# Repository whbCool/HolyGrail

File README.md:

# TEA@CPP Escape Room 2026: The Holy Grail

The _Holy Grail_ is a custom PCB, designed for the Indiana Jones puzzle as a part of TEA@CPP's "Retro Rewind" 2026 Escape Room. 

This repository includes the KiCad schematic, as well as the code database for the board.

For more details on the code, check out [the introductory walkthrough here](walkthrough.md).

Major Components:
- ESP32-WROOM-32UE
- SC16IS752IPW_128
- CD74HC138QM96Q1
- SN74LVC1G125DBVT
- CDCLVC1106PWR
- 7447715003
- LMR33640
- AP63205WU-7
- 5747842-2
- W5500
- USBLC6-2SC6
- TMJ0026ABNL
- MMBT3904
- CP2102N-A02-GQFN24
- 1812L150_24MR
- LM393DR

Design Requirements:
1. Read data from 12 LD2410C sensors using SPI-to-UART converters.
2. Aggregate sensor data and package it into a JSON payload to be sent to an MQTT broker.
3. USB port for programming and debugging.

More Info: https://drive.google.com/drive/folders/14Y64IZpTN127Q0mva5SdtTZ1QgllTaBJ

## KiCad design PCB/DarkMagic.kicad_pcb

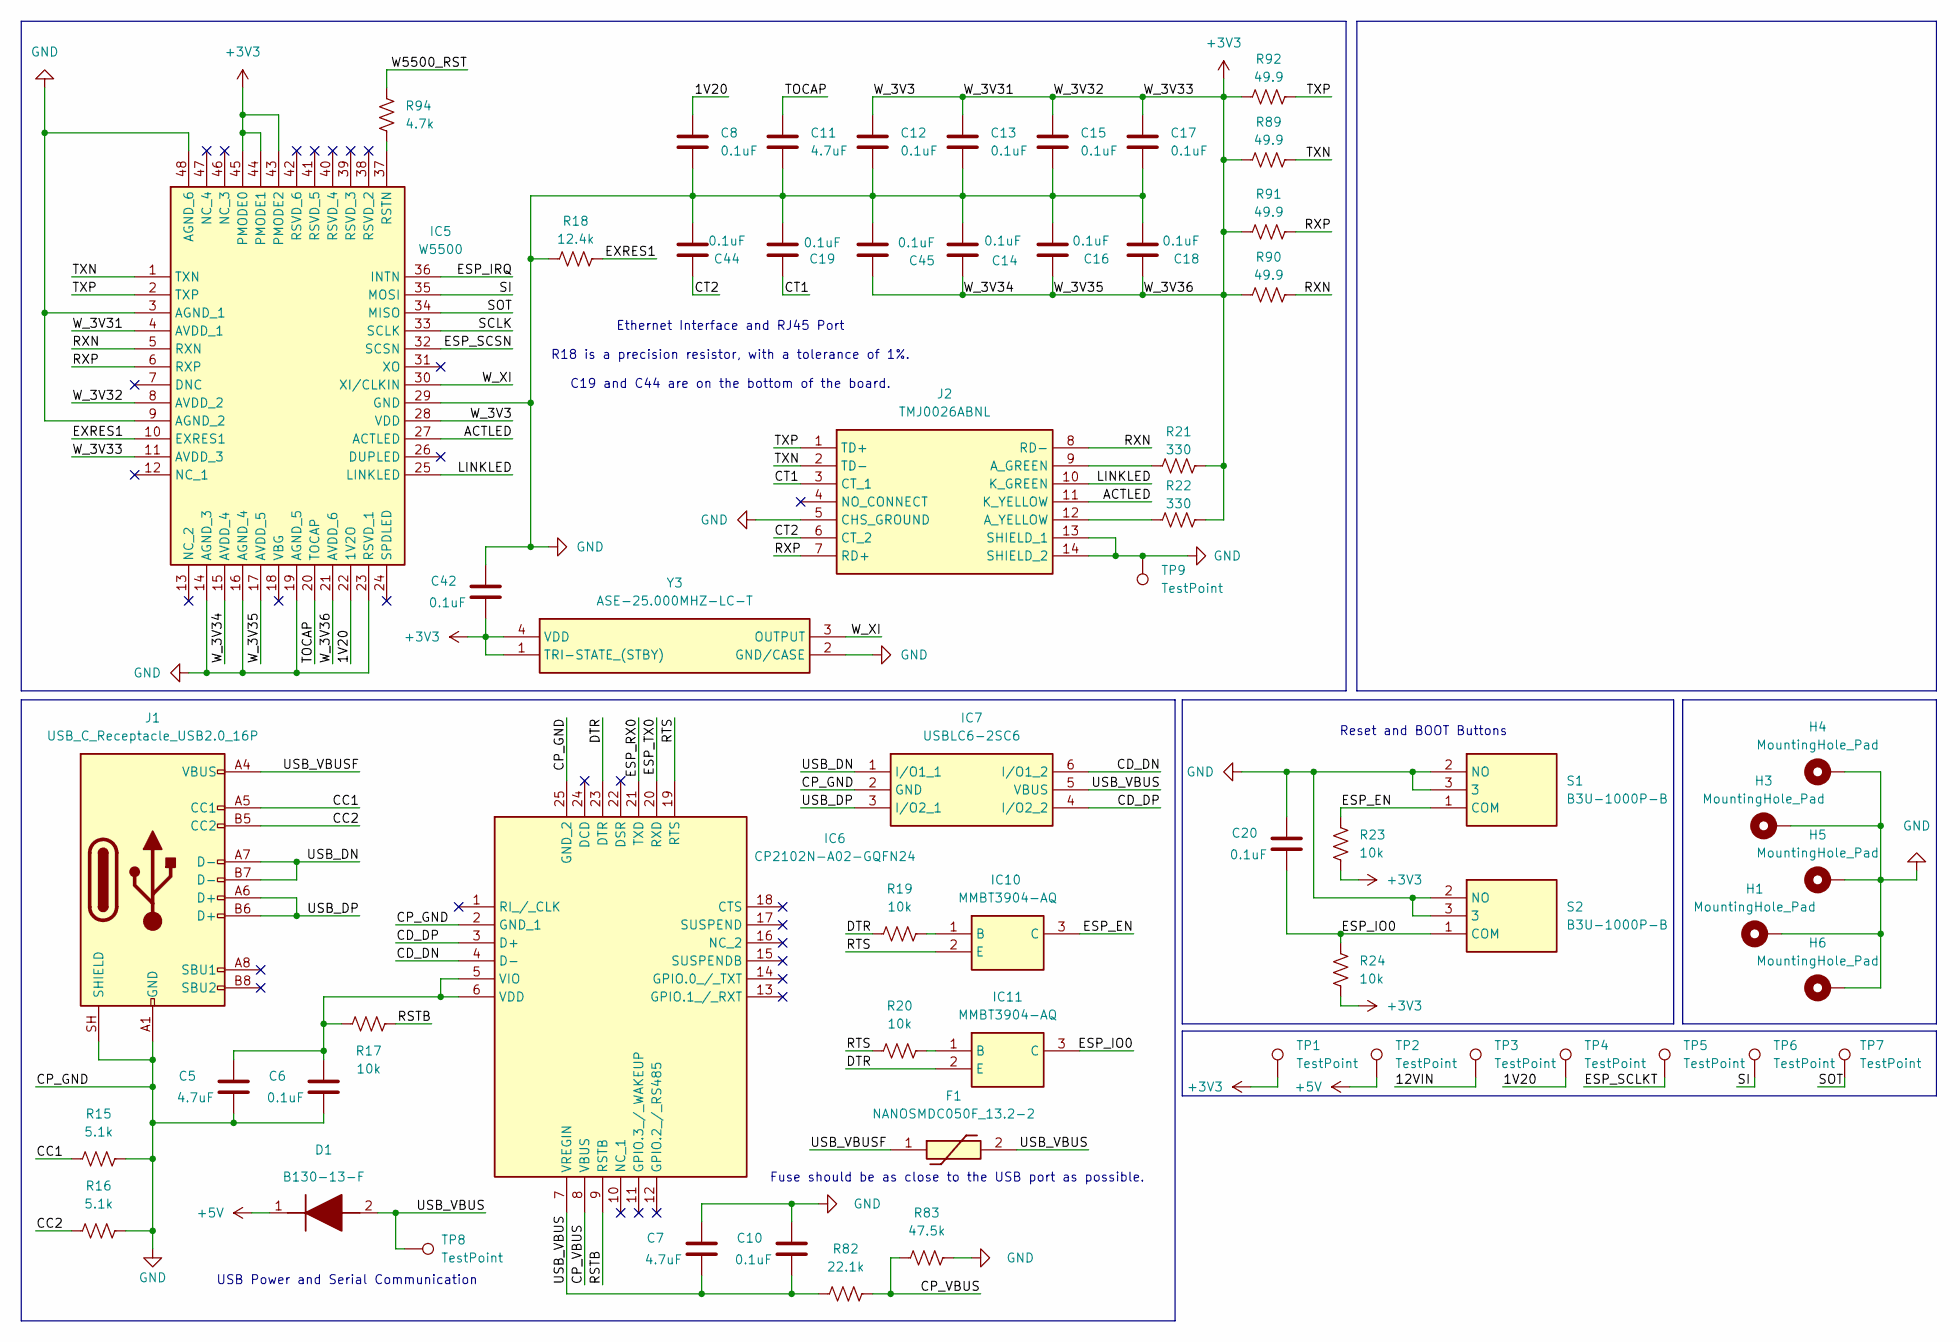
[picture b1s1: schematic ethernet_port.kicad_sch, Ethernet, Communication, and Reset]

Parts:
C5, C7: 4.7uF; C_0805_2012Metric_Pad1.18x1.45mm_HandSolder; Manufacturer_Part_Number CL21A475KACLRNC; Mouser Part Number 187-CL21A475KACLRNC
C6, C8, C10, C12, C13, C14, C15, C16, C17, C18, C19, C20, C42, C44, C45: 0.1uF; C_0805_2012Metric_Pad1.18x1.45mm_HandSolder; Manufacturer_Part_Number CL21B104KCC5PNC; Mouser Part Number 187-CL21B104KCC5PNC
C11: 4.7uF; C_0805_2012Metric_Pad1.18x1.45mm_HandSolder; Manufacturer_Part_Number CL21B103KC6WPNC; Mouser Part Number 187-CL21B103KC6WPNC
D1: B130-13-F; DIOM5226X230N; Mouser Part Number 621-B130-F
F1: NANOSMDC050F_13.2-2; FUSC3216X74N; Mouser Part Number 650-NANOC050F/13.2-2
H1, H3, H4, H5, H6: MountingHole_Pad; MountingHole_3.2mm_M3_MOD
IC5: W5500; QFP50P900X900X160-48N; Mouser Part Number 950-W5500
IC6: CP2102N-A02-GQFN24; QFN50P400X400X80-25N-D; Mouser Part Number 634-CP2102NA02GQFN24
IC7: USBLC6-2SC6; SOT95P280X145-6N; Mouser Part Number 511-USBLC6-2SC6
IC10, IC11: MMBT3904-AQ; SOT95P240X120-3N; Mouser Part Number 637-MMBT3904-AQ
J1: USB_C_Receptacle_USB2.0_16P; USB_C_Receptacle_GCT_USB4105-xx-A_16P_TopMnt_Horizontal; Manufacturer_Part_Number UJ20-C-H-G-SMT-1A-P16-TR; Mouser Part Number 179-CHGSMT1AP16TR
J2: TMJ0026ABNL; Mouser Part Number 960-TMJ0026ABNL
R15, R16: 5.1k; R_0805_2012Metric_Pad1.20x1.40mm_HandSolder; Manufacturer_Part_Number ERA-6ARB512V; Mouser Part Number 667-ERA-6ARB512V
R17, R19, R20, R23, R24: 10k; R_0805_2012Metric_Pad1.20x1.40mm_HandSolder; Manufacturer_Part_Number ERA-6AEB103V; Mouser Part Number 667-ERA-6AEB103V
R18: 12.4k; R_0805_2012Metric_Pad1.20x1.40mm_HandSolder; Manufacturer_Part_Number ERJ-UP6F1242V; Mouser Part Number 667-ERJ-UP6F1242V
R21, R22: 330; R_0805_2012Metric_Pad1.20x1.40mm_HandSolder; Manufacturer_Part_Number ERJ-PC6B3300V; Mouser Part Number 667-ERJ-PC6B3300V
R82: 22.1k; R_0805_2012Metric_Pad1.20x1.40mm_HandSolder; Manufacturer_Part_Number ERA-6AEB2212V; Mouser Part Number 667-ERA-6AEB2212V
R83: 47.5k; R_0805_2012Metric_Pad1.20x1.40mm_HandSolder; Manufacturer_Part_Number ERA-6AEB4752V; Mouser Part Number 667-ERA-6AEB4752V
R89, R90, R91, R92: 49.9; R_0805_2012Metric_Pad1.20x1.40mm_HandSolder; Manufacturer_Part_Number ERJ-P06F49R9V; Mouser Part Number 667-ERJ-P06F49R9V
R94: 4.7k; R_0805_2012Metric_Pad1.20x1.40mm_HandSolder; Manufacturer_Part_Number ERA-6AEB103V; Mouser Part Number 667-ERA-6AEB103V
S1, S2: B3U-1000P-B; B3U1000PB; Mouser Part Number 653-B3U-1000P-B
TP1, TP2, TP3, TP4, TP5, TP6, TP7, TP8, TP9: TestPoint; TestPoint_Pad_D3.0mm
Y3: ASE-25.000MHZ-LC-T; ASE25000MHZLCT; Mouser Part Number 815-ASE-25.000MHZ-LC-T

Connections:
+5V: D1.1 (K), TP2.1 (1_1); also elsewhere on the board
/1V20: C8.1, IC5.22 (1V2O), TP4.1 (1_1)
/12VIN: TP3.1 (1_1); also elsewhere on the board
/ACTLED: IC5.27 (ACTLED), J2.11 (K_YELLOW)
/CC1: J1.A5 (CC1), R15.1
/CC2: J1.B5 (CC2), R16.1
/CD_DN: IC6.4 (D-), IC7.6 (I/O1_2)
/CD_DP: IC6.3 (D+), IC7.4 (I/O2_2)
/CP_VBUS: IC6.8 (VBUS), R82.1, R83.1
/CT1: C19.2, J2.3 (CT_1)
/CT2: C44.1, J2.6 (CT_2)
/DTR: IC6.23 (DTR), IC11.2 (E), R19.1
/ESP_EN: IC10.3 (C), R23.2, S1.1 (COM); also elsewhere on the board
/ESP_IO0: C20.1, IC11.3 (C), R24.2, S2.1 (COM); also elsewhere on the board
/ESP_IRQ: IC5.36 (INTN); also elsewhere on the board
/ESP_RX0: IC6.21 (TXD); also elsewhere on the board
/ESP_SCLKT: TP5.1 (1_1); also elsewhere on the board
/ESP_SCSN: IC5.32 (SCSN); also elsewhere on the board
/ESP_TX0: IC6.20 (RXD); also elsewhere on the board
/EXRES1: IC5.10 (EXRES1), R18.2
/LINKLED: IC5.25 (LINKLED), J2.10 (K_GREEN)
/RSTB: IC6.9 (RSTB), R17.2
/RTS: IC6.19 (RTS), IC10.2 (E), R20.1
/RXN: IC5.5 (RXN), J2.8 (RD-), R90.2
/RXP: IC5.6 (RXP), J2.7 (RD+), R91.2
/SCLK: IC5.33 (SCLK); also elsewhere on the board
/SI: IC5.35 (MOSI), TP6.1 (1_1); also elsewhere on the board
/SOT: IC5.34 (MISO), TP7.1 (1_1); also elsewhere on the board
/TOCAP: C11.1, IC5.20 (TOCAP)
/TXN: IC5.1 (TXN), J2.2 (TD-), R89.2
/TXP: IC5.2 (TXP), J2.1 (TD+), R92.2
/USB_DN: IC7.1 (I/O1_1), J1.A7 (D-), J1.B7 (D-)
/USB_DP: IC7.3 (I/O2_1), J1.A6 (D+), J1.B6 (D+)
/USB_VBUS: C7.1, C10.1, D1.2 (A), F1.2, IC6.7 (VREGIN), IC7.5 (VBUS), R82.2, TP8.1 (1_1)
/USB_VBUSF: F1.1, J1.A4 (VBUS), J1.A9 (VBUS), J1.B4 (VBUS), J1.B9 (VBUS)
/W5500_RST: R94.1; also elsewhere on the board
/W_XI: IC5.30 (XI/CLKIN), Y3.3 (OUTPUT)
unnamed: IC5.37 (RSTN), R94.2
unnamed: C5.2, C6.2, IC6.5 (VIO), IC6.6 (VDD), R17.1
unnamed: IC10.1 (B), R19.2
unnamed: IC11.1 (B), R20.2
unnamed: J2.9 (A_GREEN), R21.1
unnamed: J2.12 (A_YELLOW), R22.1

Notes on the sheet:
Ethernet Interface and RJ45 Port R18 is a precision resistor, with a tolerance of 1%. C19 and C44 are on the bottom of the board.
USB Power and Serial Communication
Reset and BOOT Buttons
Fuse should be as close to the USB port as possible.

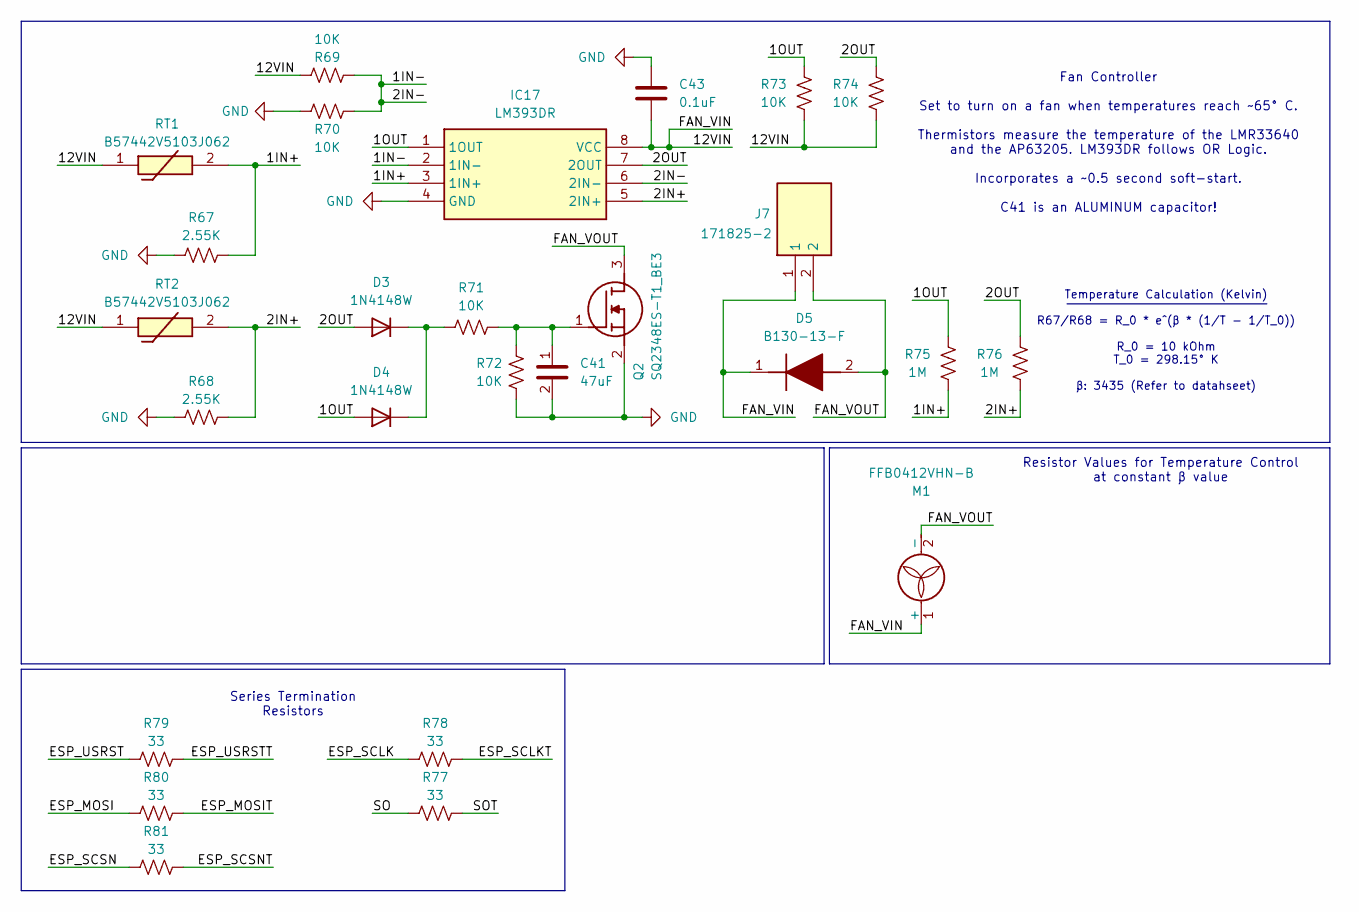
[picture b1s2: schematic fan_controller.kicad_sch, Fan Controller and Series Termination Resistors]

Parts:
C41: 47uF; C_Elec_10x10.2; Manufacturer_Part_Number EEH-ZA1K470P; Mouser Part Number 667-EEH-ZA1K470P
C43: 0.1uF; C_0805_2012Metric_Pad1.18x1.45mm_HandSolder; Manufacturer_Part_Number CL21B104KCC5PNC; Mouser Part Number 187-CL21B104KCC5PNC
D3, D4: 1N4148W; D_SOD-123; Manufacturer_Part_Number 1N4148W-7-F; Mouser Part Number 621-1N4148W-7-F
D5: B130-13-F; DIOM5226X230N; Mouser Part Number 621-B130-F
IC17: LM393DR; SOIC127P600X175-8N; Mouser Part Number 595-LM393DR
J7: 171825-2; SHDR2W69P0X250_1X2_500X530X1040P; Mouser Part Number 571-171825-2
M1: FFB0412VHN-B; Manufacturer_Part_Number FFB0412VHN-B; Mouser Part Number 108-FFB0412VHN-B
Q2: SQ2348ES-T1_BE3; SOT95P237X112-3N; Mouser Part Number 78-SQ2348ES-T1_BE3
R67, R68: 2.55K; R_0805_2012Metric_Pad1.20x1.40mm_HandSolder; Manufacturer_Part_Number ERA-6AEB2551V; Mouser Part Number 667-ERA-6AEB2551V
R69, R70, R71, R72, R73, R74: 10K; R_0805_2012Metric_Pad1.20x1.40mm_HandSolder; Manufacturer_Part_Number ERA-6APB103V; Mouser Part Number 667-ERA-6APB103V
R75, R76: 1M; R_0805_2012Metric_Pad1.20x1.40mm_HandSolder; Manufacturer_Part_Number ERA-6AEB105V; Mouser Part Number 667-ERA-6AEB105V
R77, R78, R79, R80, R81: 33; R_0805_2012Metric_Pad1.20x1.40mm_HandSolder; Manufacturer_Part_Number ERA-6AHD330V; Mouser Part Number 667-ERA-6AHD330V
RT1, RT2: B57442V5103J062; THRMC2012X130N; Mouser Part Number 871-B57442V5103J62

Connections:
/1IN+: IC17.3 (1IN+), R67.1, R75.1, RT1.2
/1IN-: IC17.2 (1IN-), IC17.6 (2IN-), R69.2, R70.1
/1OUT: D4.2 (A), IC17.1 (1OUT), R73.2, R75.2
/2IN+: IC17.5 (2IN+), R68.1, R76.1, RT2.2
/2OUT: D3.2 (A), IC17.7 (2OUT), R74.2, R76.2
/12VIN: C43.2, D5.1 (K), IC17.8 (VCC), J7.1, M1.1 (+), R69.1, R73.1, R74.1, RT1.1, RT2.1; also elsewhere on the board
/ESP_MOSI: R80.2; also elsewhere on the board
/ESP_MOSIT: R80.1; also elsewhere on the board
/ESP_SCLK: R78.2; also elsewhere on the board
/ESP_SCLKT: R78.1; also elsewhere on the board
/ESP_SCSN: R81.2; also elsewhere on the board
/ESP_SCSNT: R81.1; also elsewhere on the board
/ESP_USRST: R79.2; also elsewhere on the board
/ESP_USRSTT: R79.1; also elsewhere on the board
/FAN_VOUT: D5.2 (A), J7.2, M1.2 (-), Q2.3 (D)
/SO: R77.2; also elsewhere on the board
/SOT: R77.1; also elsewhere on the board
unnamed: D3.1 (K), D4.1 (K), R71.1
unnamed: C41.1, Q2.1 (G), R71.2, R72.2

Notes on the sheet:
Resistor Values for Temperature Control at constant β value
Series Termination Resistors
Fan Controller Set to turn on a fan when temperatures reach ~65° C. Thermistors measure the temperature of the LMR33640 and the AP63205. LM393DR follows OR Logic. Incorporates a ~0.5 second soft-start. C41 is an ALUMINUM capacitor!
Temperature Calculation (Kelvin) R67/R68 = R_0 * e^(β * (1/T - 1/T_0)) R_0 = 10 kOhm T_0 = 298.15° K β: 3435 (Refer to datahseet)

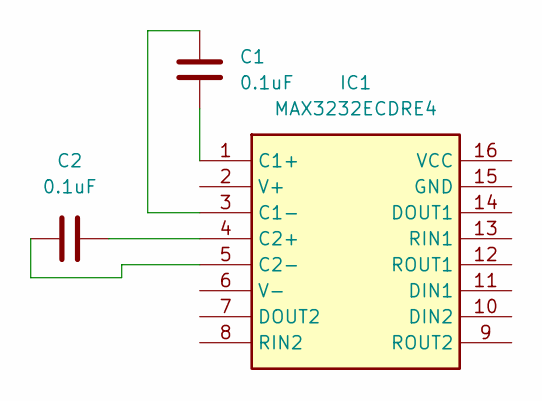
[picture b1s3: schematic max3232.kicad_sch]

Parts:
C1, C2: 0.1uF
IC1: MAX3232ECDRE4; SOIC127P600X175-16N; Manufacturer_Part_Number MAX3232ECDRE4; Mouser Part Number 595-MAX3232ECDRE4

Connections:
/XS1T: IC1.6 (Y4); also elsewhere on the board
/XS3T: IC1.14 (Y1); also elsewhere on the board
/XS4T: IC1.9 (Y5); also elsewhere on the board
/XS5T: IC1.11 (Y2); also elsewhere on the board
/XS6T: IC1.13 (Y3); also elsewhere on the board

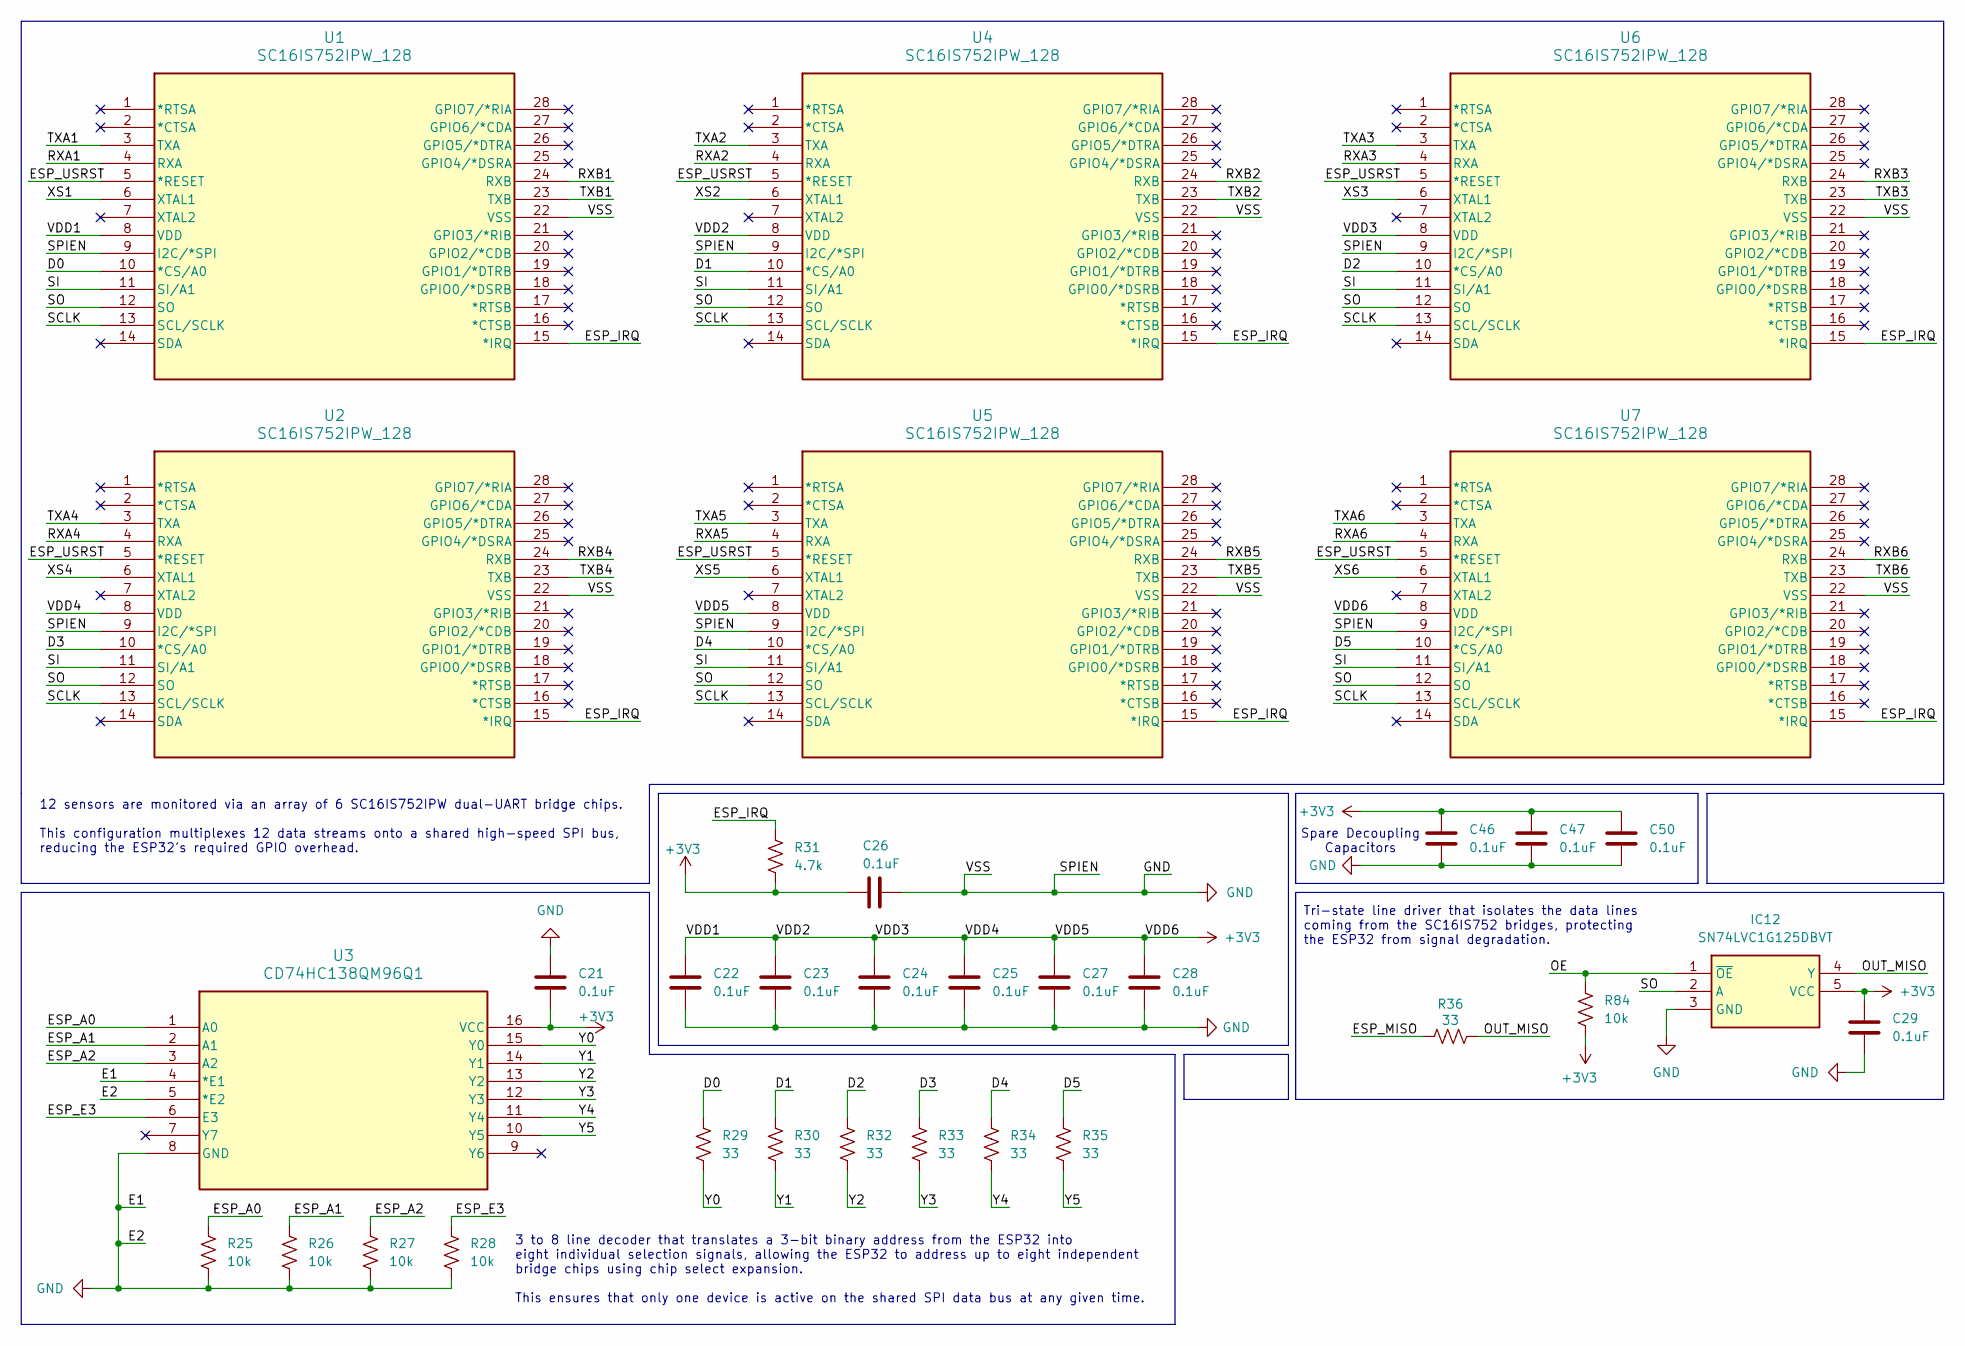
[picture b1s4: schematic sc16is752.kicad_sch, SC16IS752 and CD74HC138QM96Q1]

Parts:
C21, C22, C23, C24, C25, C26, C27, C28, C29, C46, C47, C50: 0.1uF; C_0805_2012Metric_Pad1.18x1.45mm_HandSolder; Manufacturer_Part_Number CL21B104KCC5PNC; Mouser Part Number 187-CL21B104KCC5PNC
IC12: SN74LVC1G125DBVT; SOT95P280X145-5N; Mouser Part Number 595-SN74LVC1G125DBVR
R25, R26, R27, R28, R84: 10k; R_0805_2012Metric_Pad1.20x1.40mm_HandSolder; Manufacturer_Part_Number ERA-6AEB103V; Mouser Part Number 667-ERA-6AEB103V
R29, R30, R32, R33, R34, R35, R36: 33; R_0805_2012Metric_Pad1.20x1.40mm_HandSolder; Manufacturer_Part_Number ERA-6AHD330V; Mouser Part Number 667-ERA-6AHD330V
R31: 4.7k; R_0805_2012Metric_Pad1.20x1.40mm_HandSolder; Manufacturer_Part_Number ERJ-UP6D4701V; Mouser Part Number 667-ERJ-UP6D4701V
U1, U2, U4, U5, U6, U7: SC16IS752IPW_128; TSSOP28_SOT361-1_NXP; Manufacturer_Part_Number SC16IS752IPW,128; Mouser Part Number 771-SC16IS752IPW128
U3: CD74HC138QM96Q1; D16; Manufacturer_Part_Number CD74HC138QM96Q1; Mouser Part Number 595-CD74HC138QM96Q1

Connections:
/D0: R29.1, U1.10 (*CS/A0)
/D1: R30.1, U4.10 (*CS/A0)
/D2: R32.1, U6.10 (*CS/A0)
/D3: R33.1, U2.10 (*CS/A0)
/D4: R34.1, U5.10 (*CS/A0)
/D5: R35.1, U7.10 (*CS/A0)
/ESP_A0: R25.1, U3.1 (A0); also elsewhere on the board
/ESP_A1: R26.1, U3.2 (A1); also elsewhere on the board
/ESP_A2: R27.1, U3.3 (A2); also elsewhere on the board
/ESP_E3: R28.2, U3.6 (E3); also elsewhere on the board
/ESP_IRQ: R31.2, U1.15 (*IRQ), U2.15 (*IRQ), U4.15 (*IRQ), U5.15 (*IRQ), U6.15 (*IRQ), U7.15 (*IRQ); also elsewhere on the board
/ESP_MISO: R36.1; also elsewhere on the board
/ESP_USRST: U1.5 (*RESET), U2.5 (*RESET), U4.5 (*RESET), U5.5 (*RESET), U6.5 (*RESET), U7.5 (*RESET); also elsewhere on the board
/OE: IC12.1 (~OE), R84.1; also elsewhere on the board
/OUT_MISO: IC12.4 (Y), R36.2
/RXA1: U1.4 (RXA); also elsewhere on the board
/RXA2: U4.4 (RXA); also elsewhere on the board
/RXA3: U6.4 (RXA); also elsewhere on the board
/RXA4: U2.4 (RXA); also elsewhere on the board
/RXA5: U5.4 (RXA); also elsewhere on the board
/RXA6: U7.4 (RXA); also elsewhere on the board
/RXB1: U1.24 (RXB); also elsewhere on the board
/RXB2: U4.24 (RXB); also elsewhere on the board
/RXB3: U6.24 (RXB); also elsewhere on the board
/RXB4: U2.24 (RXB); also elsewhere on the board
/RXB5: U5.24 (RXB); also elsewhere on the board
/RXB6: U7.24 (RXB); also elsewhere on the board
/SCLK: U1.13 (SCL/SCLK), U2.13 (SCL/SCLK), U4.13 (SCL/SCLK), U5.13 (SCL/SCLK), U6.13 (SCL/SCLK), U7.13 (SCL/SCLK); also elsewhere on the board
/SI: U1.11 (SI/A1), U2.11 (SI/A1), U4.11 (SI/A1), U5.11 (SI/A1), U6.11 (SI/A1), U7.11 (SI/A1); also elsewhere on the board
/SO: IC12.2 (A), U1.12 (SO), U2.12 (SO), U4.12 (SO), U5.12 (SO), U6.12 (SO), U7.12 (SO); also elsewhere on the board
/TXA1: U1.3 (TXA); also elsewhere on the board
/TXA2: U4.3 (TXA); also elsewhere on the board
/TXA3: U6.3 (TXA); also elsewhere on the board
/TXA4: U2.3 (TXA); also elsewhere on the board
/TXA5: U5.3 (TXA); also elsewhere on the board
/TXA6: U7.3 (TXA); also elsewhere on the board
/TXB1: U1.23 (TXB); also elsewhere on the board
/TXB2: U4.23 (TXB); also elsewhere on the board
/TXB3: U6.23 (TXB); also elsewhere on the board
/TXB4: U2.23 (TXB); also elsewhere on the board
/TXB5: U5.23 (TXB); also elsewhere on the board
/TXB6: U7.23 (TXB); also elsewhere on the board
/XS1: U1.6 (XTAL1); also elsewhere on the board
/XS2: U4.6 (XTAL1); also elsewhere on the board
/XS3: U6.6 (XTAL1); also elsewhere on the board
/XS4: U2.6 (XTAL1); also elsewhere on the board
/XS5: U5.6 (XTAL1); also elsewhere on the board
/XS6: U7.6 (XTAL1); also elsewhere on the board
/Y0: R29.2, U3.15 (Y0)
/Y1: R30.2, U3.14 (Y1)
/Y2: R32.2, U3.13 (Y2)
/Y3: R33.2, U3.12 (Y3)
/Y4: R34.2, U3.11 (Y4)
/Y5: R35.2, U3.10 (Y5)

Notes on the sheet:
3 to 8 line decoder that translates a 3-bit binary address from the ESP32 into eight individual selection signals, allowing the ESP32 to address up to eight independent bridge chips using chip select expansion. This ensures that only one device is active on the shared SPI data bus at any given time.
Tri-state line driver that isolates the data lines coming from the SC16IS752 bridges, protecting the ESP32 from signal degradation.
Spare Decoupling Capacitors
12 sensors are monitored via an array of 6 SC16IS752IPW dual-UART bridge chips. This configuration multiplexes 12 data streams onto a shared high-speed SPI bus, reducing the ESP32's required GPIO overhead.

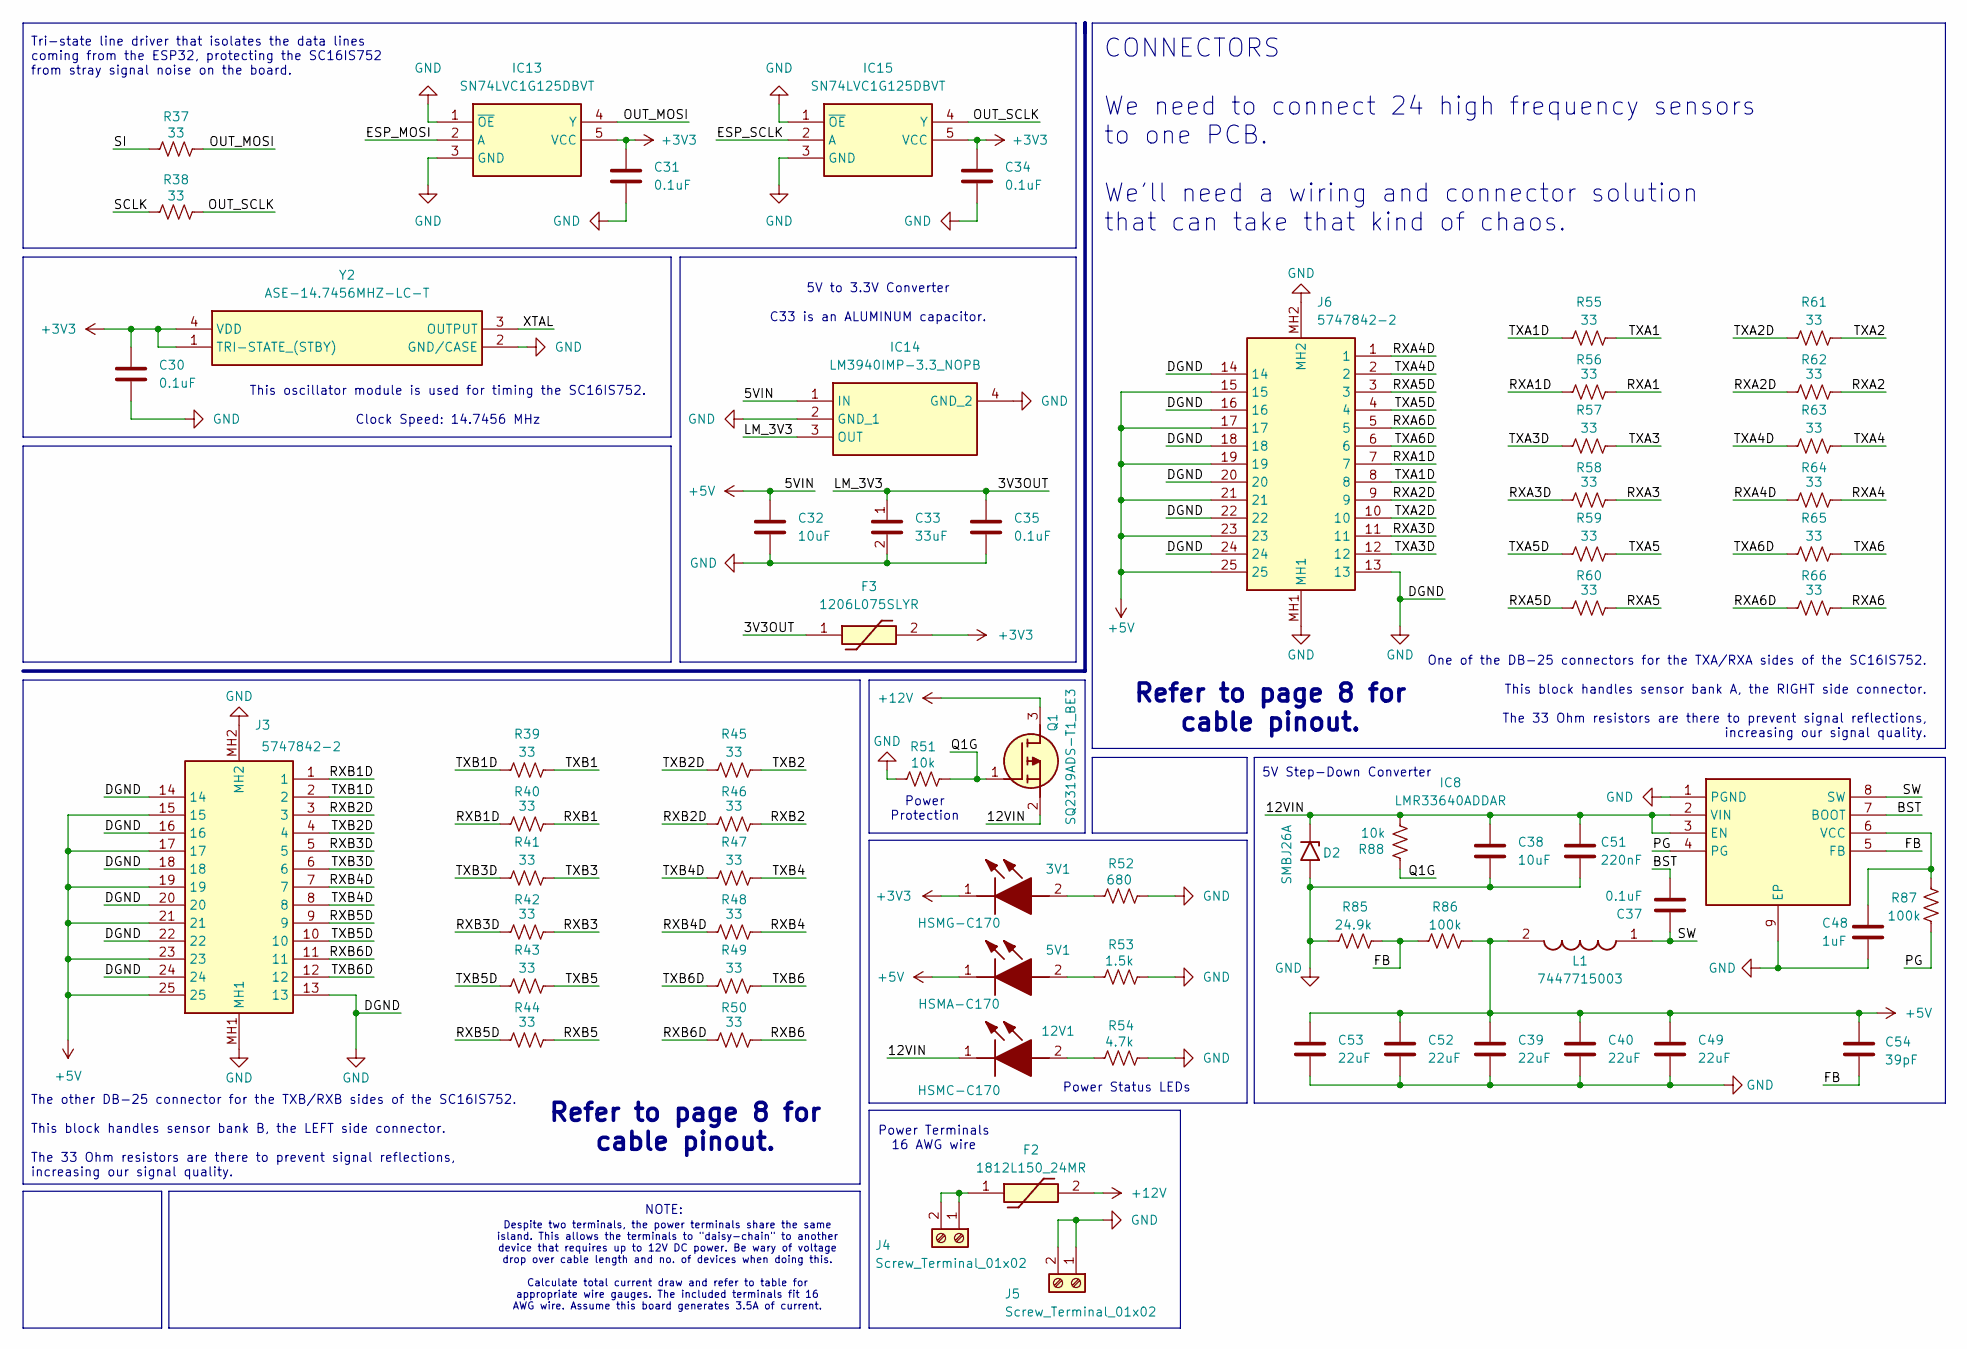
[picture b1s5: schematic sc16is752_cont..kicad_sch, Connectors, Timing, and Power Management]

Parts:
3V1: HSMG-C170; LEDC2012X80N; Mouser Part Number 630-HSMG-C170
5V1: HSMA-C170; LEDC2012X90N; Mouser Part Number 630-HSMA-C170
12V1: HSMC-C170; LEDC2012X90N; Mouser Part Number 630-HSMC-C170
C30, C31, C34, C35, C37: 0.1uF; C_0805_2012Metric_Pad1.18x1.45mm_HandSolder; Manufacturer_Part_Number CL21B104KCC5PNC; Mouser Part Number 187-CL21B104KCC5PNC
C32, C38: 10uF; C_0805_2012Metric_Pad1.18x1.45mm_HandSolder; Manufacturer_Part_Number CL21A106KBYQNNE; Mouser Part Number 187-CL21A106KBYQNNE
C33: 33uF; C_Elec_10x10.2; Manufacturer_Part_Number EEH-ZA1K330P; Mouser Part Number 667-EEH-ZA1K330P
C39, C40, C49, C52, C53: 22uF; C_0805_2012Metric_Pad1.18x1.45mm_HandSolder; Manufacturer_Part_Number CL21X226MQQNNNG; Mouser Part Number 187-CL21X226MQQNNNG
C48: 1uF; C_0805_2012Metric_Pad1.18x1.45mm_HandSolder; Manufacturer_Part_Number CL21B105KOFNNWE; Mouser Part Number 187-CL21B105KOFNNWE
C51: 220nF; C_0805_2012Metric_Pad1.18x1.45mm_HandSolder; Manufacturer_Part_Number CL21B224KBFNFNE; Mouser Part Number 187-CL21B224KBFNFNE
C54: 39pF; C_0805_2012Metric_Pad1.18x1.45mm_HandSolder; Manufacturer_Part_Number CL21C390JBANNNC; Mouser Part Number 187-CL21C390JBANNNC
D2: SMBJ26A; D_SMA; Manufacturer_Part_Number SMBJ26A; Mouser Part Number 576-SMBJ26A
F2: 1812L150_24MR; 1812L010DR; Mouser Part Number 576-1812L150/24MR
F3: 1206L075SLYR; Fuse_1206_3216Metric; Mouser Part Number 576-1206L075SLYR
IC8: LMR33640ADDAR; SOIC127P600X170-9N; Mouser Part Number 595-LMR33640ADDAR
IC13, IC15: SN74LVC1G125DBVT; SOT95P280X145-5N; Mouser Part Number 595-SN74LVC1G125DBVR
IC14: LM3940IMP-3.3_NOPB; SOT230P700X180-4N; Mouser Part Number 926-LM3940IMP3.3NOPB
J3, J6: 5747842-2; 57478422; Mouser Part Number 737-DB25-SA-M2
J4, J5: Screw_Terminal_01x02; TerminalBlock_Ningbo-Kagnex_HB9500M_1x02_P9.5mm; Manufacturer_Part_Number YK6010223000G; Mouser Part Number 649-YK6010223000G
L1: 7447715003; L_12x12mm_H4.5mm; Mouser Part Number 710-7447715003
Q1: SQ2319ADS-T1_BE3; SOT95P237X112-3N; Mouser Part Number 78-SQ2319ADS-T1_BE3
R37, R38, R39, R40, R41, R42, R43, R44, R45, R46, R47, R48, R49, R50, R55, R56, R57, R58, R59, R60, R61, R62, R63, R64, R65, R66: 33; R_0805_2012Metric_Pad1.20x1.40mm_HandSolder; Manufacturer_Part_Number ERA-6AHD330V; Mouser Part Number 667-ERA-6AHD330V
R51, R88: 10k; R_0805_2012Metric_Pad1.20x1.40mm_HandSolder; Manufacturer_Part_Number ERA-6AEB103V; Mouser Part Number 667-ERA-6AEB103V
R52: 680; R_0805_2012Metric_Pad1.20x1.40mm_HandSolder; Manufacturer_Part_Number ERJ-S06J681V; Mouser Part Number 667-ERJ-S06J681V
R53: 1.5k; R_0805_2012Metric_Pad1.20x1.40mm_HandSolder; Manufacturer_Part_Number ERA-6AEB152V; Mouser Part Number 667-ERA-6AEB152V
R54: 4.7k; R_0805_2012Metric_Pad1.20x1.40mm_HandSolder; Manufacturer_Part_Number ERJ-UP6D4701V; Mouser Part Number 667-ERJ-UP6D4701V
R85: 24.9k; R_0805_2012Metric_Pad1.20x1.40mm_HandSolder; Manufacturer_Part_Number ERJ-PB6B2492V; Mouser Part Number 667-ERJ-PB6B2492V
R86, R87: 100k; R_0805_2012Metric_Pad1.20x1.40mm_HandSolder; Manufacturer_Part_Number ERA-6AEB104V; Mouser Part Number 667-ERA-6AEB104V
Y2: ASE-14.7456MHZ-LC-T; ASE24576MHZLCT; Mouser Part Number 815-ASE14.7456MHZLCT

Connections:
+5V: 5V1.1 (K), C32.2, C39.2, C40.2, C49.2, C52.2, C53.2, C54.1, IC14.1 (IN), J3.15, J3.17, J3.19, J3.21, J3.23, J3.25, J6.15, J6.17, J6.19, J6.21, J6.23, J6.25, L1.2, R86.2; also elsewhere on the board
+12V: F2.2, Q1.3 (D)
/3V3OUT: C33.1, C35.2, F3.1, IC14.3 (OUT)
/12VIN: 12V1.1 (K), C38.2, C51.2, D2.1 (A1), IC8.2 (VIN), IC8.3 (EN), Q1.2 (S), R88.1; also elsewhere on the board
/BST: C37.1, IC8.7 (BOOT)
/ESP_MOSI: IC13.2 (A); also elsewhere on the board
/ESP_SCLK: IC15.2 (A); also elsewhere on the board
/FB: C54.2, IC8.5 (FB), R85.2, R86.1
/OUT_MOSI: IC13.4 (Y), R37.2
/OUT_SCLK: IC15.4 (Y), R38.2
/PG: IC8.4 (PG), R87.2
/Q1G: Q1.1 (G), R51.2, R88.2
/RXA1: R56.2; also elsewhere on the board
/RXA1D: J6.7, R56.1
/RXA2: R62.2; also elsewhere on the board
/RXA2D: J6.9, R62.1
/RXA3: R58.2; also elsewhere on the board
/RXA3D: J6.11, R58.1
/RXA4: R64.2; also elsewhere on the board
/RXA4D: J6.1, R64.1
/RXA5: R60.2; also elsewhere on the board
/RXA5D: J6.3, R60.1
/RXA6: R66.2; also elsewhere on the board
/RXA6D: J6.5, R66.1
/RXB1: R40.2; also elsewhere on the board
/RXB1D: J3.1, R40.1
/RXB2: R46.2; also elsewhere on the board
/RXB2D: J3.3, R46.1
/RXB3: R42.2; also elsewhere on the board
/RXB3D: J3.5, R42.1
/RXB4: R48.2; also elsewhere on the board
/RXB4D: J3.7, R48.1
/RXB5: R44.2; also elsewhere on the board
/RXB5D: J3.9, R44.1
/RXB6: R50.2; also elsewhere on the board
/RXB6D: J3.11, R50.1
/SCLK: R38.1; also elsewhere on the board
/SI: R37.1; also elsewhere on the board
/SW: C37.2, IC8.8 (SW), L1.1
/TXA1: R55.2; also elsewhere on the board
/TXA1D: J6.8, R55.1
/TXA2: R61.2; also elsewhere on the board
/TXA2D: J6.10, R61.1
/TXA3: R57.2; also elsewhere on the board
/TXA3D: J6.12, R57.1
/TXA4: R63.2; also elsewhere on the board
/TXA4D: J6.2, R63.1
/TXA5: R59.2; also elsewhere on the board
/TXA5D: J6.4, R59.1
/TXA6: R65.2; also elsewhere on the board
/TXA6D: J6.6, R65.1
/TXB1: R39.2; also elsewhere on the board
/TXB1D: J3.2, R39.1
/TXB2: R45.2; also elsewhere on the board
/TXB2D: J3.4, R45.1
/TXB3: R41.2; also elsewhere on the board
/TXB3D: J3.6, R41.1
/TXB4: R47.2; also elsewhere on the board
/TXB4D: J3.8, R47.1
/TXB5: R43.2; also elsewhere on the board
/TXB5D: J3.10, R43.1
/TXB6: R49.2; also elsewhere on the board
/TXB6D: J3.12, R49.1
unnamed: 3V1.2 (A), R52.1
unnamed: 5V1.2 (A), R53.1
unnamed: 12V1.2 (A), R54.1
unnamed: C48.2, IC8.6 (VCC), R87.1
unnamed: F2.1, J4.1, J4.2

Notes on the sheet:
Despite two terminals, the power terminals share the same island. This allows the terminals to "daisy-chain" to another device that requires up to 12V DC power. Be wary of voltage drop over cable length and no. of devices when doing this. Calculate total current draw and refer to table for appropri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
Refer to page 8 for cable pinout.
NOTE:
The other DB-25 connector for the TXB/RXB sides of the SC16IS752. This block handles sensor bank B, the LEFT side connector. The 33 Ohm resistors are there to prevent signal reflections, increasing our signal quality.
Power Terminals 16 AWG wire
5V to 3.3V Converter C33 is an ALUMINUM capacitor.
5V Step-Down Converter
Refer to page 8 for cable pinout.
CONNECTORS We need to connect 24 high frequency sensors to one PCB. We'll need a wiring and connector solution that can take that kind of chaos.
Tri-state line driver that isolates the data lines coming from the ESP32, protecting the SC16IS752 from stray signal noise on the board.
Power Protection
Power Status LEDs
One of the DB-25 connectors for the TXA/RXA sides of the SC16IS752. This block handles sensor bank A, the RIGHT side connector. The 33 Ohm resistors are there to prevent signal reflections, increasing our signal quality.
This oscillator module is used for timing the SC16IS752. Clock Speed: 14.7456 MHz

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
